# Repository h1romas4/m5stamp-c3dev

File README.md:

# m5stamp-c3dev

This is a development board for the [M5Stamp C3](https://shop.m5stack.com/products/m5stamp-c3-mate-with-pin-headers) (RISC-V/FreeRTOS).

**Hardware**

- External USB-C port for JTAG debugging
- Support for LCD panel and SD card
- Selecting a power supply
- Switch(GPIO9) to enter loader mode
- Pin headers to expose usable GPIOs to the outside
- The size is just Japanese business card

**Sample Sources Included**

- TrueType font with Japanese output to LCD - [test_freetype.cpp](https://github.com/h1romas4/m5stamp-c3dev/blob/main/main/test_freetype.cpp)
- Output PNG images in SD card to LCD - [test_tinypng.cpp](https://github.com/h1romas4/m5stamp-c3dev/blob/main/main/test_tinypng.cpp)
- NTP synchronization via WiFi connection - [test_nvs_wifi.cpp](https://github.com/h1romas4/m5stamp-c3dev/blob/main/main/test_nvs_wifi.cpp)
- Test ADC on GPIO0
    - UNIT Light - [main.cpp](https://github.com/h1romas4/m5stamp-c3dev/blob/main/main/main.cpp#L108-L111)
- Test I2C on GPIO18, 19
    - UNIT ENV III - [test_i2c_gpio1819.cpp](https://github.com/h1romas4/m5stamp-c3dev/blob/main/main/test_i2c_gpio1819.cpp#L43-L50)
    - UNIT ULTRASONIC - [test_i2c_gpio1819.cpp](https://github.com/h1romas4/m5stamp-c3dev/blob/main/main/test_i2c_gpio1819.cpp#L52-L61)
- Test UART on GPIO18, 19
    - UNIT GPS - [test_uart_gpio1819.cpp](https://github.com/h1romas4/m5stamp-c3dev/blob/main/main/test_uart_gpio1819.cpp)
- WebAssembly execution with Wasm3
    - Analog clock using AssemblyScript - [test_wasm3_clockenv.cpp](https://github.com/h1romas4/m5stamp-c3dev/blob/main/main/test_wasm3_clockenv.cpp)
    - GPS GSV viewer using AssemblyScript - [test_wasm3_gpsgsv.cpp](https://github.com/h1romas4/m5stamp-c3dev/blob/main/main/test_wasm3_gpsgsv.cpp)
    - 3D Cube Demo using AssemblyScript - [test_wasm3_imu6886.cpp](https://github.com/h1romas4/m5stamp-c3dev/blob/main/main/test_wasm3_imu6886.cpp)
- Usage of SPIFFS, which stores TrueType fonts and .wasm binaries (parttool.py and spiffsgen.py tools)
- Use of NVS (cryptographically enabled key value store) that stores WiFi passwords (nvs_partition_gen.py tool)
- Building libraries and managing dependencies using the esp-idf build system
- Visual Studio Code C/C++ Extension configuration and JTAG debugging configuration in conjunction with openocd
- AssembyScript sharing method between web browser and microcontroller - [wasm](https://github.com/h1romas4/m5stamp-c3dev/tree/main/wasm)

This repository contains MIT Licensed PCB data and example programs.

## Demo

### Video

- 📼 [Demo(LCD)](https://youtu.be/46I3Uo5Xivg)
- 📼 [Demo(Wasm3)](https://youtu.be/TagQuPtwKCg)
- 📼 [Demo(3D Cube)](https://twitter.com/h1romas4/status/1610228824607985664)

### Web Simulation

- 🕸 [AssemblyScript Analog Clock](https://h1romas4.github.io/m5stamp-c3dev/asclock/)
- 🕸 [AssemblyScript GPS GSV Viewer](https://h1romas4.github.io/m5stamp-c3dev/asgps/)

## Schematic

|#Unit|Name|Note|Where to get it|
|----|----|----|----|
|U1|AE-USB2.0-TYPE-C|USB 2.0 Type-C Break out board|[akizukidenshi.com (JP)](https://akizukidenshi.com/catalog/g/gK-13080/)|
|U2|M5STAMP-C3|M5Stamp C3|+ [M5Stack](https://shop.m5stack.com/products/m5stamp-c3-mate-with-pin-headers?variant=40724631257260)<br />+ [SWITCH SCIENCE (JP)](https://www.switch-science.com/catalog/7474/)|
|U3|KMR-1.8SPI|KMR-1.8 SPI marked LCD and SD card interface|+ [amazon.co.jp (1)](https://www.amazon.co.jp/gp/product/B07RG8SJVB/)<br />+ [ja.aliexpress.com](https://ja.aliexpress.com/item/4000511275898.html)|
|R1 - R2|5.2K Resistor|Pull-down for USB Power supply|-|
|R3 - R7|10K Resistor|SPI pull-up|-|
|JP1|Jumper pin|Select external power supply|[akizukidenshi.com (JP)](https://akizukidenshi.com/catalog/g/gP-03687/)|
|SW1|Tact switch|for loader mode and utility|[akizukidenshi.com (JP)](https://akizukidenshi.com/catalog/g/gP-03647/)|
|J1|12 Pin header|You can use the one that comes with the M5Stamp C3 Mate|-|

## PCB and Gerber data

- [KiCad 6 PCB](https://github.com/h1romas4/m5stamp-c3dev/tree/main/pcb/fg06-c3dev-revb)
- [Gerber Data](https://github.com/h1romas4/m5stamp-c3dev/raw/main/pcb/fg06-c3dev-revb/fg06-c3dev-revb-gerber.zip)
- [FG06-C3DEV REV.B (2枚) - M5Stamp C3 向けの開発用基板 - 部品なし基板のみ - 130円](https://h1romas4.booth.pm/items/3688492)

## Example Source

### Require

- [Setup ESF-IDF **release/v5.1**](https://docs.espressif.com/projects/esp-idf/en/release-v5.1/esp32c3/get-started/linux-macos-setup.html)

get_idf or (Windows) ESP-IDF command prompt

```
# Linux or macOS ->
$ alias get_idf='. $HOME/esp/esp-idf/export.sh'
$ get_idf
# <-

Detecting the Python interpreter
... snip ...
Done! You can now compile ESP-IDF projects.
Go to the project directory and run:

  idf.py build

$ echo ${IDF_PATH}
/home/hiromasa/devel/toolchain/esp/esp-idf

$ riscv32-esp-elf-gcc -v
Using built-in specs.
COLLECT_GCC=riscv32-esp-elf-gcc
... snip ...
gcc version 12.2.0 (crosstool-NG esp-12.2.0_20230208)
```

openocd (Optional)

```
$ openocd -v
Open On-Chip Debugger v0.12.0-esp32-20240318 (2024-03-18-18:25)
Licensed under GNU GPL v2
For bug reports, read
        http://openocd.org/doc/doxygen/bugs.html
```

### Build and Execute

1. git clone and build (Please add `--recursive`)

```
git clone --recursive https://github.com/h1romas4/m5stamp-c3dev
cd m5stamp-c3dev
idf.py build
```

**Note**: If you get a compile error, change the `sdkconfig` back to the Git one. In some cases, the target of `sdkconfig` is changed to `esp32` instead of `eps32c3`.

2. Write Partition table

```
idf.py partition-table-flash
```

3. Write TypeType font to SPIFFS

```
parttool.py write_partition --partition-name=font --partition-subtype=spiffs --input resources/spiffs_font.bin
```

4. Write WebAssembly(.wasm) to SPIFFS

```
parttool.py write_partition --partition-name=wasm --partition-subtype=spiffs --input resources/spiffs_wasm.bin
```

5. Write main program to go!

```
idf.py flash monitor
```

### Setup WiFi (Optional)

1. Change WiFi Setting

`nvs_partition.csv`: Set own `[ssid]`, `[password]`

```
key,type,encoding,value
wifi,namespace,,
ssid,data,string,[ssid]
passwd,data,string,[password]
```

2. Create NVS Partition file

```
python ${IDF_PATH}/components/nvs_flash/nvs_partition_generator/nvs_partition_gen.py generate nvs_partition.csv nvs_partition.bin 0x6000
```

3. Write NVS Partition

```
esptool.py write_flash 0x9000 nvs_partition.bin
```

4. Run

NTP synchronization is performed by pressing the SW1 after the startup logo.

```
idf.py monitor
```

### Select connected GPIO18 and GPIO19 device (Optional)

```
idf.py menuconfig
```

C3DEV Configuration → Select GPIO 18/19

`3D Cube Demo`

### JTAG debug with Visual Studio Code

Require setup ESP32_TOOLCHAIN_HOME

```
$ echo ${ESP32_TOOLCHAIN_HOME}
/home/hiromasa/.espressif/tools/riscv32-esp-elf
```

1. Connect the PC to the USB Type-C of the U1
2. Open the source file in Visual Studio Code.
3. Run Task "openocd (debug)" @see [.vscode/tasks.json](https://github.com/h1romas4/m5stamp-c3dev/blob/main/.vscode/tasks.json#L7-L13)
4. Set a breakpoint in the source code.
5. Debug Launch (GDB) @see [.vscode/launch.json](https://github.com/h1romas4/m5stamp-c3dev/blob/main/.vscode/launch.json#L8-L23)
    The first time you start the program, it will often fail, so if you get an error, retry.

### Note

#### If the LCD color is inverted.

`main/main.cpp`

```c
    // If the color is inverted, set to 1.
    tft.invertDisplay(0);
    // tft.invertDisplay(1);
```

#### Create SPIFFS partition file from file system

```
python ${IDF_PATH}/components/spiffs/spiffsgen.py 0x100000 resources/font resources/spiffs_font.bin
python ${IDF_PATH}/components/spiffs/spiffsgen.py 0x10000 resources/wasm resources/spiffs_wasm.bin
```

#### Change the output destination of the log to U1 Serial/JTAG.(Don't forget to put it back)

Component config → ESP System Settings → Channel for console output

```
idf.py menuconfig
```

## AssemblyScript and Wasm3

## Build AssemblyScript

```
cd wasm/clockenv # or wasm/gpsgsv or wasm/imu6886
npm install
```

**Web Browser Development**

```
npm run asbuild:web
npm run start
# http://localhost:1234/
```

**SPIFFS Build and Flash**

```
npm run asbuild
cd ../../
python ${IDF_PATH}/components/spiffs/spiffsgen.py 0x10000 resources/wasm resources/spiffs_wasm.bin
parttool.py write_partition --partition-name=wasm --partition-subtype=spiffs --input resources/spiffs_wasm.bin
```

## Dependencies

Thanks for all the open source.

|Name|Version|License|
|-|-|--|
|[esp-idf](https://docs.espressif.com/projects/esp-idf/en/release-v5.1/esp32c3/get-started/index.html)|`release/v5.1`|BSD License|
|[arduino-esp32](https://github.com/espressif/arduino-esp32/releases/tag/3.0.2)|`3.0.2`|LGPL-2.1 License|
|[M5EPD](https://github.com/m5stack/M5EPD)|`0.1.5`|MIT License|
|[UNIT_ENV](https://github.com/m5stack/UNIT_ENV)|`0.0.7`|MIT License|
|[M5Unit-Sonic](https://github.com/m5stack/M5Unit-Sonic)|`0.0.2`|MIT License|
|[Adafruit_GFX](https://github.com/adafruit/Adafruit-GFX-Library)|`1.11.9`|BSD License|
|[Adafruit_BusIO](https://github.com/adafruit/Adafruit_BusIO)|`1.16.1`|MIT License|
|[Adafruit-ST7735-Library](https://github.com/adafruit/Adafruit-ST7735-Library)|`1.10.4`|MIT License|
|[tinyPNG](https://github.com/olliiiver/tinyPNG)|`0.11`|MIT License|
|[lwgps](https://github.com/MaJerle/lwgps)|`v2.1.0`|MIT License|
|[Wasm3](https://github.com/wasm3/wasm3)|master(`045040a9`)|MIT License|
|[AssemblyScript](https://github.com/AssemblyScript/assemblyscript)|`0.27.29`|Apache-2.0 License|
|[源真ゴシック](http://jikasei.me/font/genshin/)|-|SIL Open Font License 1.1|

## License

MIT License (includes PCB data and example source)

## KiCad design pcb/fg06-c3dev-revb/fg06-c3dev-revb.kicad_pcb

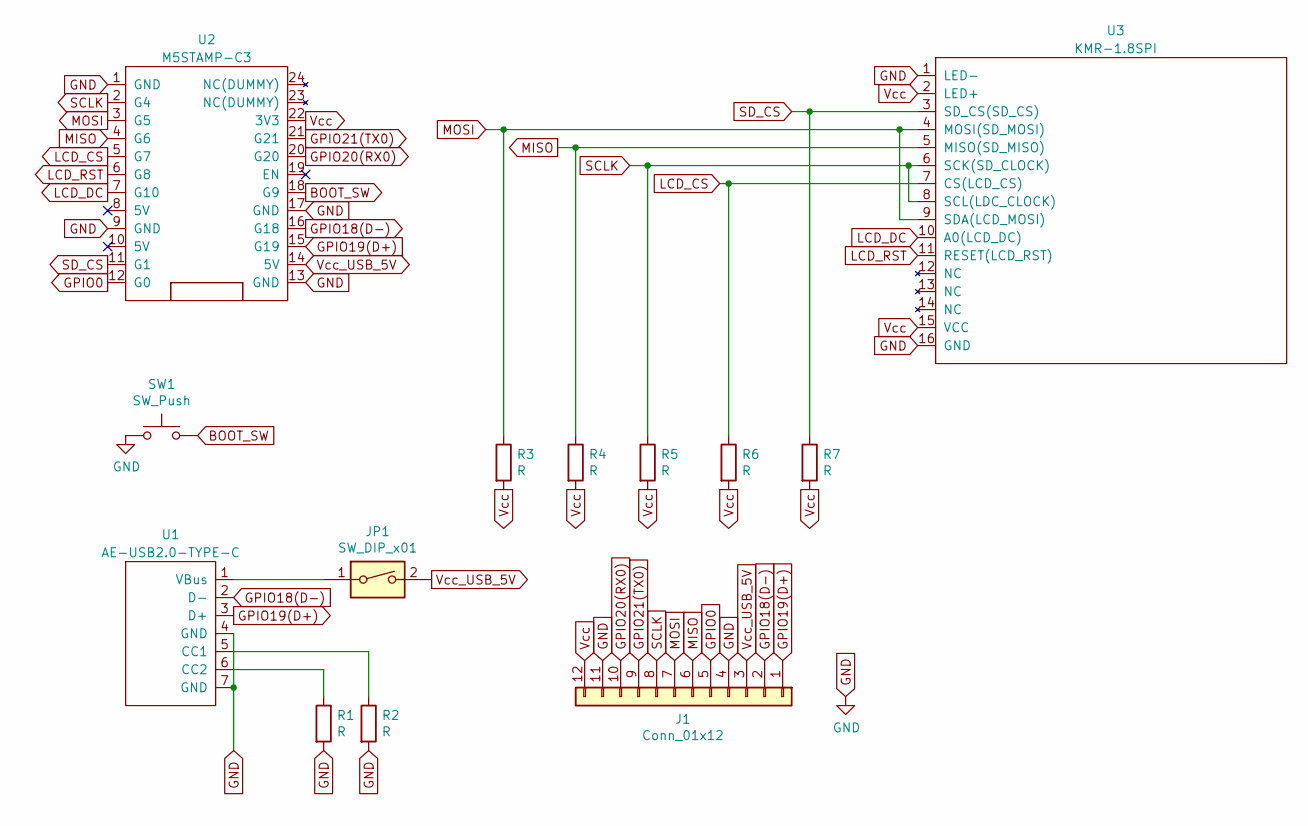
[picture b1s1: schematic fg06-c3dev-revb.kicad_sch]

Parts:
J1: Conn_01x12; PinHeader_1x12_P2.54mm_Vertical
JP1: SW_DIP_x01; PinHeader_1x02_P2.54mm_Vertical
R1, R2, R3, R4, R5, R6, R7: R; R_Axial_DIN0207_L6.3mm_D2.5mm_P7.62mm_Horizontal
SW1: SW_Push; SW_PUSH_6mm
U1: AE-USB2.0-TYPE-C
U2: M5STAMP-C3
U3: KMR-1.8SPI

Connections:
BOOT_SW: SW1.2, U2.18 (G9)
GND: J1.4, J1.11, R1.2, R2.2, SW1.1, U1.4 (GND), U1.7 (GND), U2.1 (GND), U2.9 (GND), U2.13 (GND), U2.17 (GND), U3.1 (LED-), U3.16 (GND)
GPIO0: J1.5, U2.12 (G0)
GPIO18(D-): J1.2, U1.2 (D-), U2.16 (G18)
GPIO19(D+): J1.1, U1.3 (D+), U2.15 (G19)
GPIO20(RX0): J1.10, U2.20 (G20)
GPIO21(TX0): J1.9, U2.21 (G21)
LCD_CS: R6.1, U2.5 (G7), U3.7 (CS(LCD_CS))
LCD_DC: U2.7 (G10), U3.10 (A0(LCD_DC))
LCD_RST: U2.6 (G8), U3.11 (RESET(LCD_RST))
MISO: J1.6, R4.1, U2.4 (G6), U3.5 (MISO(SD_MISO))
MOSI: J1.7, R3.1, U2.3 (G5), U3.4 (MOSI(SD_MOSI)), U3.9 (SDA(LCD_MOSI))
unnamed: JP1.1, U1.1 (VBus)
unnamed: R1.1, U1.6 (CC2)
unnamed: R2.1, U1.5 (CC1)
SCLK: J1.8, R5.1, U2.2 (G4), U3.6 (SCK(SD_CLOCK)), U3.8 (SCL(LDC_CLOCK))
SD_CS: R7.1, U2.11 (G1), U3.3 (SD_CS(SD_CS))
Vcc: J1.12, R3.2, R4.2, R5.2, R6.2, R7.2, U2.22 (3V3), U3.2 (LED+), U3.15 (VCC)
Vcc_USB_5V: J1.3, JP1.2, U2.14 (5V)

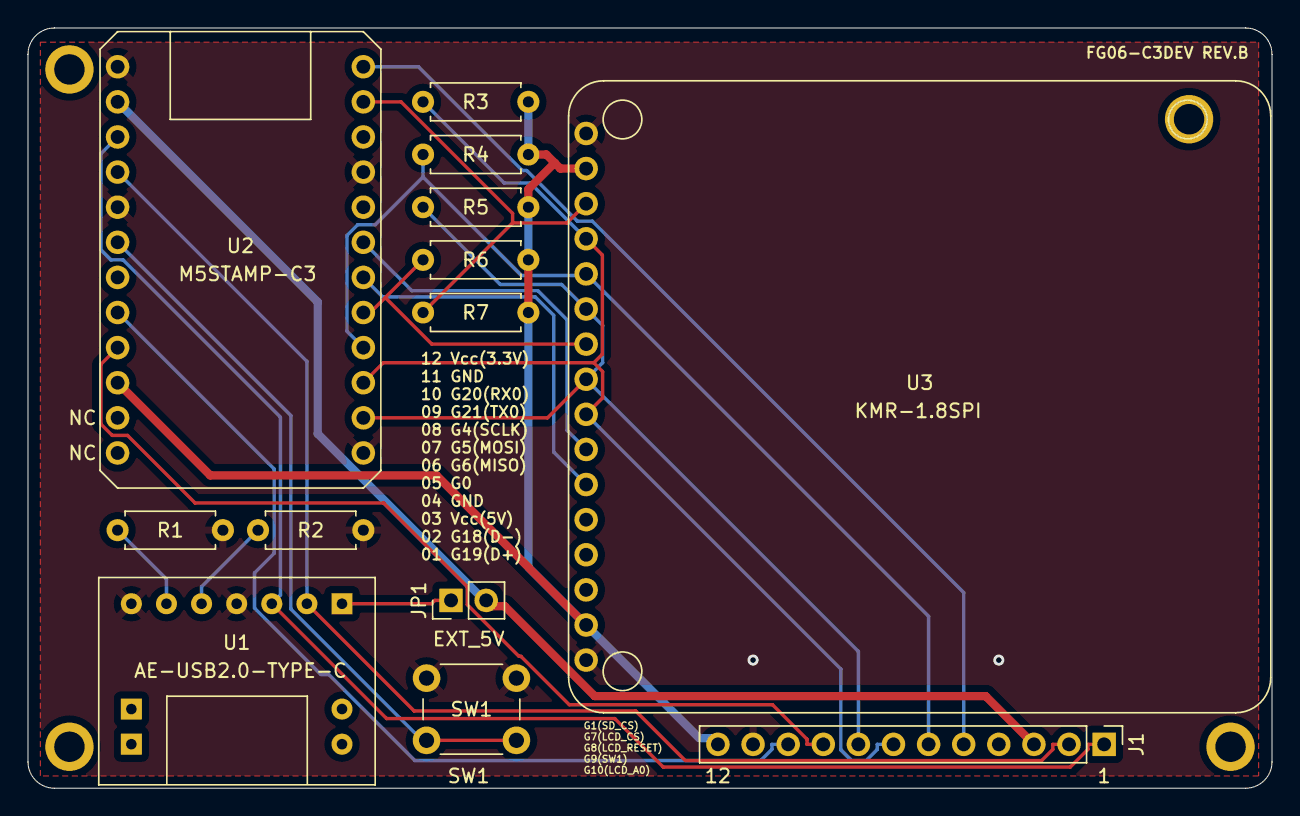
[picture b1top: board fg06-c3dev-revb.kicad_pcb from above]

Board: 2 copper layers, 90.0 x 55.0 mm, 17 parts (0 on the bottom side), 19 nets.

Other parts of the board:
REF1, REF2, REF3, REF4: Pad; MountingHole_2.2mm_M2_ISO7380_Pad

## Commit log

2021-12-31 fix anot
2021-12-31 fix footprint
2021-12-31 place
2022-01-01 ignore fp-info-cache
2022-01-15 update pcb
2022-01-15 add gerber
2022-02-20 add extensions.json
2022-02-21 change directory structure
2022-02-21 add License
2022-02-23 add wasm3
2022-02-23 fix CMakeists.txt
2022-02-23 add wasm
2022-02-23 lipstick
2022-02-23 wasm (WIP)
2022-02-24 fix wasm build (NativeMathf)
2022-02-25 update wasm3
2022-02-25 fix file name
2022-02-25 wasm3 (WIP)
2022-02-25 add wasm3 circle
2022-02-25 fix file name...
2022-02-26 WIP (All the variables under this will be broken)
2022-02-26 add .gitignore
2022-02-27 add env.abort
2022-02-27 add backtrace
2022-02-27 add note
2022-02-27 add memory limit
2022-02-27 add debug
2022-02-27 minimize partition
2022-02-27 fix lowMemoryLimit
2022-02-27 add tasks
2022-03-01 split test
2022-03-01 comment logs
2022-03-01 fix stack size
2022-03-01 comment out that not everyone can perform
2022-03-01 remove unnessesary
2022-03-01 add unit_env (WIP)
2022-03-02 disable JTAG (WIP...)
2022-03-04 update arduino-esp32
2022-03-05 add comment (WIP)
2022-03-05 add support unitenv
2022-03-05 add delay
2022-03-05 add compile option tinypng -fexceptions
2022-03-05 screen adjustment
2022-03-05 fix tft invert color
2022-03-13 update wasm
2022-03-13 tick!
2022-03-15 fix interface
2022-03-15 add color
2022-03-15 fix test
2022-03-15 add web test
2022-03-16 fix spell
2022-03-16 add color exchange
2022-03-16 add support string
2022-03-16 add support draw_line
2022-03-16 add NativeMathf
2022-03-17 add support nvs patition
2022-03-17 add support NTP
2022-03-18 add line
2022-03-18 fix r
2022-03-19 add AssemblyScript Analog Clock
2022-03-19 add docs
2022-03-19 fix context path
2022-03-19 add unit env
2022-03-20 update web
2022-03-20 update web wasm
2022-03-20 add dot by dot style
2022-03-20 dot by dot
2022-03-21 fix hour..
2022-03-21 fix hour...
2022-03-21 add partition
2022-03-21 fix timezone
2022-03-21 add assemblyscript lisence
2022-03-24 add gitignore
2022-03-24 gerber data update (There are no modifications to the circuit. More accurate correction of screw hole position)
2022-03-24 add compile option
2022-03-24 add enviii stub
2022-03-24 sync ntp and reboot
2022-03-25 fix .gitignore
2022-03-25 remove unused
2022-03-25 remove log
2022-03-28 add unitenv iii
2022-03-29 fix submodule
2022-03-29 fix tasks
2022-03-29 fix vscode setting
2022-03-29 fir Windows
2022-03-29 fix miss merge
2022-03-29 add i2c comment
2022-03-29 change i2c reassignment logic
2022-03-29 split nvs and wifi
2022-03-29 add comment
2022-04-08 update dependencies
2022-04-08 add github actions
2022-04-08 add wasm build
2022-04-08 fix github actions
2022-04-08 fix github actions build
2022-04-08 add build badge
2022-04-14 add support SK6812
2022-04-14 add support RGB LED color
2022-05-23 add unit gps
2022-05-30 add kconnfig (WIP)
2022-08-04 update GitHub Actions
2022-08-04 update library dependencies
2022-08-04 fix license
2022-08-04 extends partitions
2022-08-04 set to default gpio1819
2022-08-04 add support select i2c device
2022-08-04 update AssemblyScript
2022-08-04 fix WiFi and DHCP (esp-idf 4.4.2...)
2022-08-05 update AssemblyScript module
2022-08-05 Refactor code. Use Mathf (f32 variant) everywhere
2022-08-05 better
2022-08-05 more
2022-08-05 Use int abs
2022-08-06 fix typo
2022-08-06 fix version arduino-esp32
2022-08-07 split wasm
2022-08-07 recreate SPIFFS image
2022-08-07 fix log TAG name
2022-08-07 init wasm-gps
2022-08-07 add gps dependencies
2022-08-07 add gps test
2022-08-07 to no_std 50KB
2022-08-08 add support lwgps
2022-08-08 add test GPS
2022-08-09 update toolchaine path
2022-08-11 add support UNIT Light
2022-08-11 fix GPIO18, 19 config
2022-08-11 add support unit ultrasonic
2022-08-11 add support unit ultrasonic (2)
2022-08-11 add support ultrasonic (3)
2022-08-11 update sdk config
2022-08-11 update README (1)
2022-08-11 Revert "update github actions"
    This reverts commit acf255adf4b4ef7477b95da635fc4dbc13b51b23.
2022-08-11 Revert "update README"
    This reverts commit 4aa0b5c8e4a8593ac26a8fa6a3ceed3641e4b831.
2022-08-11 Revert "update README (1)"
    This reverts commit 0dfb78918a802557078734900f93d87ffb794df5.
2022-08-11 Revert "Merge commit 'a7757c3e668804c4362e98fe7e54df606160a765'"
    This reverts commit 098ee0d0ddea31d70c9ea795dfc5150f21949986, reversing
    changes made to c7b3bb06b2b15d0286e2183cce563784db41ad9c.
2022-08-11 Revert "Revert "Merge commit 'a7757c3e668804c4362e98fe7e54df606160a765'""
    This reverts commit 1c12eb3f5e8cb344a3e736a05b6862340c909c64.
2022-08-11 update github pages package
2022-08-11 fix Math to Mathf
2022-08-12 fix comment
2022-08-12 enable GPS test
2022-08-13 add gpsgsv view with AssemblyScript (WIP)
2022-08-13 add gpsgsv wasm support
2022-08-13 update wasm spiffs
2022-08-13 add gpsgsv wasm loader
2022-08-13 add wasn interface
2022-08-13 see you next day!
2022-08-13 optimize
2022-08-14 add support GPS!
2022-08-14 update DEMO
2022-08-14 fix typo...
2022-08-17 add toolchaine cache for github actions
2022-08-17 use toolchaine cache
2022-08-17 use toolchaine cache (fix)
2022-08-17 test build in cache
2022-09-11 add support unit ir
2022-09-11 fix cmake
2022-10-10 update arduino 2.0.5 and dependencies
2022-10-17 fix kicad 3d model path
2022-10-20 add support debug to restart
2022-10-29 optimize draw freetype
2022-12-04 update wasm3 and remove workaround
2023-01-01 add support wasm3 linker flags
2023-01-01 add support transaction in SPI
2023-01-01 update wasm binary on Web
2023-01-03 add 3d cube (WIP)
2023-01-03 fix spi transaction and screen resolution
2023-01-03 update kconfig
2023-01-04 change wasm3 compile option
2023-01-05 add comment (benchmark)
2023-01-05 update github actions (ubuntu 22.04)
2023-01-06 update Adafruit_BusIO
2023-01-07 remove unuserd
2023-01-07 add tsconfig
2023-01-13 to camel case
2023-01-28 update vscode debug launch config
2023-02-03 update Adafruit_GFX
2023-03-01 updare esp-idf to 4.4.4 and arduino-esp32 to 2.0.7
2023-03-18 remove git dependencies.lock
2023-04-27 update AssemblyScript to 0.27.4 and dev dependencies
2023-08-20 upgrade esp-idf v4.4.5 and arduino-esp32 v2.0.11
2023-08-20 upgrade AssemblyScript 0.27.9
2023-08-20 upgrade js dependencies
2023-08-21 update esp32 lib dependencies
2023-10-12 add support clangd (LSP)
2023-10-13 update lcd dependencies
2023-10-27 add .gitignore (clangd)
2023-10-27 Revert "add .gitignore (clangd)"
    This reverts commit a7d41ccf46d76a075353ee00731c49e04cd7a970.
2024-07-07 upgrade esp-idf to release/v5.1
2024-07-10 temporary remove IRemoteESP8266
2024-07-10 fix build error in printf format
2024-07-10 temporary remove led
2024-07-10 update kcd drivers
2024-07-21 update sdkconfig
